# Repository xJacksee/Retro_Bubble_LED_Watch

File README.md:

# Retro Bubble LED Watch
Retro Bubble LED Watch is a project dedicated to infamous HP's bubble LED seven segment displays produced around 1970s. The goal of this project is to create fully functional retro watch from scratch (including code) based around modern components while the aforementioned display being the centerpiece.

## Project's goal
Retro Bubble LED Watch is a project dedicated to infamus HP's bubble LED seven segment displays produced around 1970s. The goal of this project is to create fully functional retro watch from scratch (including code) based around modern components while the afordmentioned display being the centerpiece.

## Components
The circuit features ATMega328PB microcontroller fulfilling the role as the display multiplexer and I2C communicator with RTC module. For the RTC IC a popular DS1337 has been chosen due it's low standby power, wide supplay voltage range and low price point. Along with this IC comes an external precision quartz crystal designed for digital watches. Due to space limitations a standard 3V CR2032 lithium coin battery supplies power to the circuit. The capacity as well as the footprint of this power source is quite large and thus the rough estimated lifetime of single cell might be as long as 2,5 years while normal use.

## Features
- Display time with precision to tenths of seconds
- Date and numbered day of the week (1 - monday etc.) display
- Temperature measurement by uC's built-in sensor (requires individual calibration)
- 2 independent alarms
- Optional external buzzer activated on alarm trigger
- SPI pins accesable for easy reprogramming
- 2 buttons for activating display/changing modes and time/date/alarm setting

## Dependencies
The programme has been written in Arduino using only Wire library. To upload the code it is nessesary to install and add Mini-Core library to Arduino IDE. The fuse bits settings for ATmega328PB have to be left at factory default (including clock - internal 8MHz RC colock have been used) according to official Microchip datasheet.

## Temperature sensor calibration
Please refer to to ATmega328PB's datasheet section 28.8. "Temperature Measurement" or AVR122 application note. Every MCU requires individual calibration. In this project, a single point calibration method was used. The offset value can be tuned in source code by changing the value of "T_OFFSET" definition.

## External buzzer
Due to space limitations, an alarm buzzer couldn't be fitted on the PCB. Solder pads J2 provide a connection to the PE0 pin of MCU that turns on periodacly during the alarm. External piezoelectric disc can be connected to these pads and fitted onto the internal surface of the lid. The buzzer must not consume more than 40mA otherwise MCU can be damaged. 

## Case
The case is designed to be 3D printed using any material. Supports are nessesary.

## Battery life and current consumption
The CR2032 battery has the capacity to power the circuit for over 2 years but the accurate battery life is dependant on frequency of turing on the display which can consume up to 35mA in peak. This loads the battery and the voltage drop can couse the uC to shutdown when battery is drained. While in sleep the circuit consumes, according to manufacturers' datasheets maximum of arund 5uA in worst case scenario.

## Authors
Szymon Bartosik

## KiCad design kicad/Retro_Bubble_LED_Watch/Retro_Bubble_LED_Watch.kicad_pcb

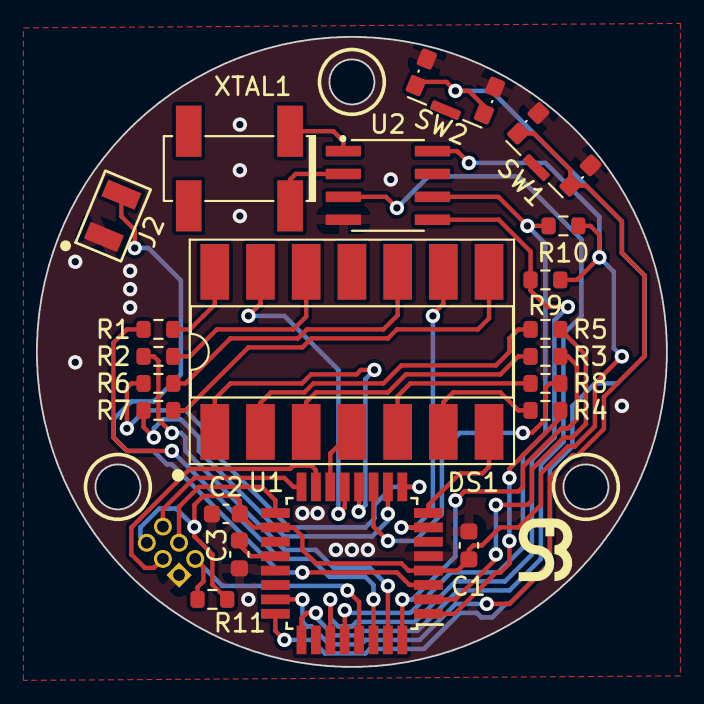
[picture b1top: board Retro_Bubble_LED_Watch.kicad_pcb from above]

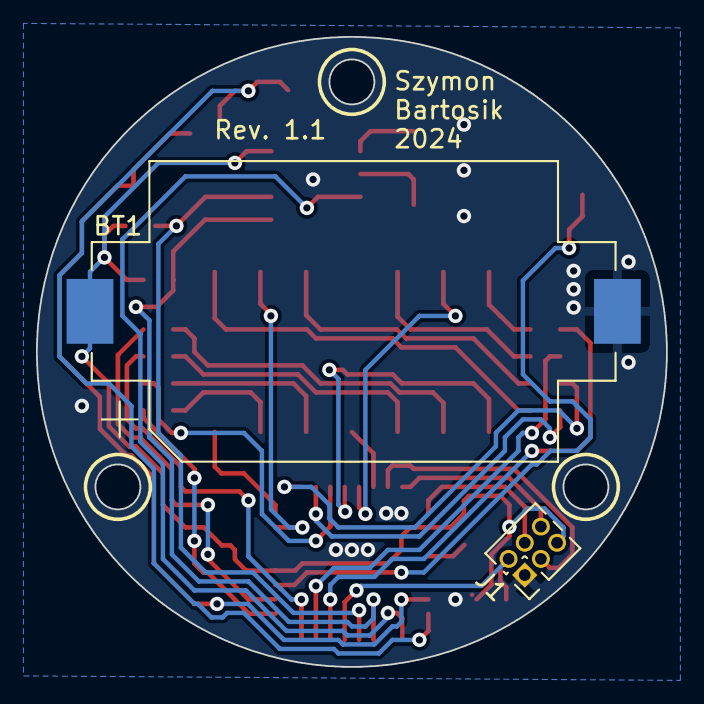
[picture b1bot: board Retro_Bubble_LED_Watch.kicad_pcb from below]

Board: 2 copper layers, 35.0 x 35.0 mm, 23 parts (2 on the bottom side), 36 nets.

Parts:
BT1: Panasonic CR2032/BN; BatteryHolder_Keystone_1060_1x2032
C1, C2, C3: 100n; C_0603_1608Metric
DS1: HP 5082-7415; DIP-14_W8.89mm_SMDSocket_LongPads
J1: ISP Programming Connector; PinHeader_2x03_P1.27mm_Vertical
J2: Pad Connector; Pad_Conn_2x1_2x1mm_2.54mm
R1, R2, R3, R4, R5, R6, R7, R8: 330R; R_0603_1608Metric
R9, R10, R11: 10k; R_0603_1608Metric
SW1, SW2: KMS231G; SW_SPST_CK_KMS2xxG
U1: ATmega328PB-A; TQFP-32_7x7mm_P0.8mm
U2: DS1337S+; SOIC127P600X175-8N
XTAL1: LFXTAL016178Reel

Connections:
+BATT: BT1.1 (+), C1.1, C2.1, J1.5, R9.1, R10.1, R11.1, U1.4 (VCC), U1.18 (AVCC), U2.8 (VCC)
/MISO: J1.6, U1.16 (PB4)
/MODE_BUTTON: SW1.1, U1.23 (PC0)
/MOSI: J1.3, U1.15 (PB3)
/SCK: J1.4, U1.17 (PB5)
/SCL: R10.2, U1.28 (PC5), U2.6 (SCL)
/SDA: R9.2, U1.27 (PC4), U2.5 (SDA)
/UP_BUTTON: SW2.1, U1.24 (PC1)
/~INTA: U1.25 (PC2), U2.3 (~INTA)
/~RESET: J1.2, R11.2, U1.29 (~RESET/PC6)
GND: BT1.2 (-), C1.2, C2.2, C3.2, J1.1, J2.1, SW1.2, SW2.2, U1.5 (GND), U1.21 (GND), U2.4 (GND)
unnamed: DS1.1 (CA1), U1.12 (PB0)
unnamed: DS1.13 (CA2), U1.13 (PB1)
unnamed: DS1.4 (CA3), U1.14 (PB2)
unnamed: DS1.9 (CA4), U1.7 (XTAL1/PB6)
unnamed: DS1.7 (CA5), U1.8 (XTAL2/PB7)
unnamed: DS1.5 (DP), R8.2
unnamed: DS1.14 (a), R1.2
unnamed: DS1.12 (b), R2.2
unnamed: DS1.3 (c), R3.2
unnamed: DS1.6 (d), R4.2
unnamed: DS1.2 (e), R5.2
unnamed: DS1.10 (f), R6.2
unnamed: DS1.8 (g), R7.2
unnamed: J2.2, U1.3 (PE0)
unnamed: C3.1, U1.20 (AREF)
unnamed: R1.1, U1.30 (PD0)
unnamed: R2.1, U1.31 (PD1)
unnamed: R3.1, U1.32 (PD2)
unnamed: R4.1, U1.1 (PD3)
unnamed: R5.1, U1.2 (PD4)
unnamed: R6.1, U1.9 (PD5)
unnamed: R7.1, U1.10 (PD6)
unnamed: R8.1, U1.11 (PD7)
unnamed: U2.1 (X1), XTAL1.1 (X1)
unnamed: U2.2 (X2), XTAL1.4 (X2)

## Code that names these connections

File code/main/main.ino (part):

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Wiring:

Segments:
PD0 - a
PD1 - b
PD2 - c
PD3 - d
PD4 - e
PD5 - f
PD6 - g
PD7 - dp

Cathodes:
PB0 - CA1 - position 0
PB1 - CA2 - position 1
PB2 - CA3 - position 2
PB6 - CA4 - position 3
PB7 - CA5 - position 4

RTC I2C communication:
PC5 - SCL
PC4 - SDA

Buttons:
PC0 - MODE switch
PC1 - UP switch

RTC interrupts:
PC2 - RTC alarm interrupt

External components:
PE0 - 20mm 4kHz piezo disc


*/
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  //Initialize Pin Chnage Interrupts
  PCICR |= 0b00000010;  //Enable PCI for bank C
  PCIFR |= 0b00000111;  //Clear interrupt flags
  PCMSK1 |= 0b00000111; //Enable PCI for PC0, PC1 and PC2
  
  //Initialize I2C communication library
  Wire.begin();
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  rtc_write(AL1_DATE_ADDR, 0b10000001); 
  rtc_write(AL2_DATE_ADDR, 0b10000001);

  //Disable alarms by default and set ~INTA as only alarm pin (these are default values of RTC's register but have to be setup this way due to possible random changes after programming and startup)
  rtc_write(CTRL_ADDR, 0b00000000);
  
  //Clear alaram flags
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void display_write() {
    PORTB =  0b11111111;                                        //Reset B pins (reverse bias)
    PORTD = digits_array[display_ptr[menu]->digits[position]];  //Set segment configuration from digits_array look-up table
    PORTD |= (display_ptr[menu]->dots[position] << PD7);        //Add dot point bit status to current digit
    PORTB = position_array[position];                           //Add bit corresponding to position argument from position_array look-up table
    position++;                                                 //Move to next digit position
    if (position > DIGITS_COUNT - 1) {                          //Reset digit counter when last position is reached
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
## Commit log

2024-03-17 restructurized code with structs
2024-03-20 added writing data
2024-03-24 added sleep mode
2024-03-30 added alarm trigger
2024-06-29 fixed 2nd alarm
2024-06-29 changed energy source to cr2032 battery
2024-06-30 first partial layout
2024-07-02 new layout
2024-07-02 added socket and display models
2024-07-02 Create LICENSE
2024-07-06 final PCB design + gerber + initial models
2024-07-06 added PCB renderings
2024-07-06 fixed typo
2024-07-07 updated models
2024-07-07 added one strap holder
2024-07-09 finished models
2024-07-23 finished rev. 1.0
2024-10-15 Rev. 1.1
2024-11-02 Fixed remainging digit after sleep bug, added 2 refresh rates + case model tweaks for better printing
2024-11-03 fixed kicad relative path + updated stl
2025-02-13 fixed reference designators in gerber files
2025-03-28 improved schematic readability + fixed component paths
